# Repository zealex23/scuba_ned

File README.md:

# SCUBA Near Eye Display

A Near Eye Display dive computer for SCUBA Divers.

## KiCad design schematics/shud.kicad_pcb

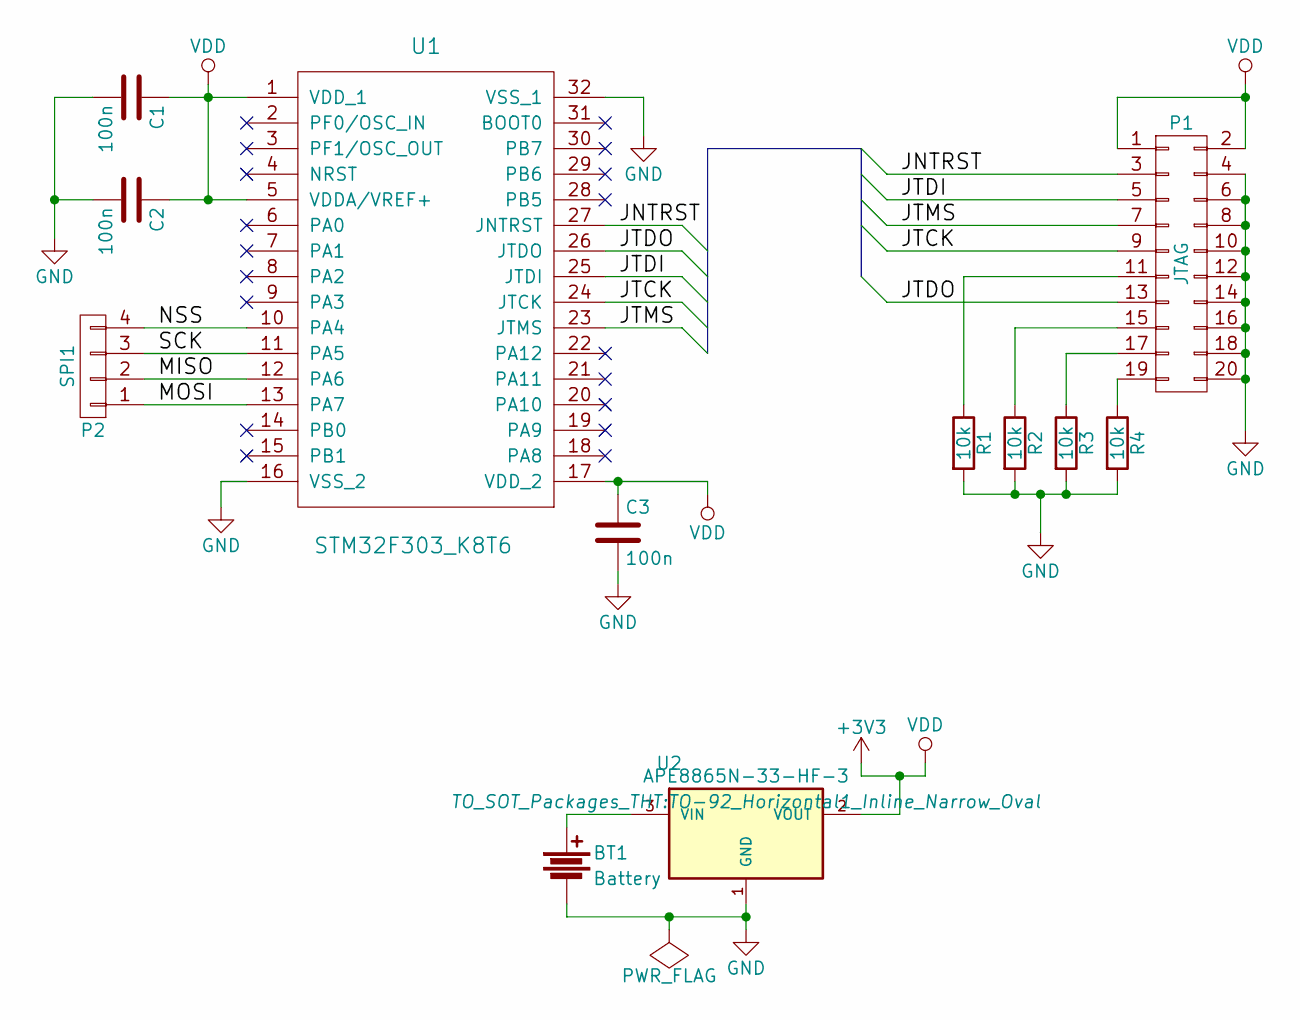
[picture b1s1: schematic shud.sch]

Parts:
BT1: Battery; TerminalBlock_Pheonix_MKDS1.5-2pol
C1, C2, C3: 100n; C_Disc_D3_P2.5
P1: JTAG; Pin_Header_Straight_2x10
P2: SPI1; Pin_Header_Straight_1x04
R1, R2, R3, R4: 10k; Resistor_Horizontal_RM10mm
U1: STM32F303_K8T6; LQFP-32_7x7mm_Pitch0.8mm
U2: APE8865N-33-HF-3; TO-92_Horizontal1_Inline_Narrow_Oval

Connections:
+3V3: C1.1, C2.1, C3.1, P1.1, P1.2, U1.1 (VDD_1), U1.5 (VDDA/VREF+), U1.17 (VDD_2), U2.2 (VOUT)
/JNTRST: P1.3, U1.27 (JNTRST)
/JTCK: P1.9, U1.24 (JTCK)
/JTDI: P1.5, U1.25 (JTDI)
/JTDO: P1.13, U1.26 (JTDO)
/JTMS: P1.7, U1.23 (JTMS)
/MISO: P2.2, U1.12 (PA6)
/MOSI: P2.1, U1.13 (PA7)
/NSS: P2.4, U1.10 (PA4)
/SCK: P2.3, U1.11 (PA5)
GND: BT1.2, C1.2, C2.2, C3.2, P1.4, P1.6, P1.8, P1.10, P1.12, P1.14, P1.16, P1.18, P1.20, R1.2, R2.2, R3.2, R4.2, U1.16 (VSS_2), U1.32 (VSS_1), U2.1 (GND)
unnamed: BT1.1, U2.3 (VIN)
unnamed: P1.11, R1.1
unnamed: P1.15, R2.1
unnamed: P1.17, R3.1
unnamed: P1.19, R4.1

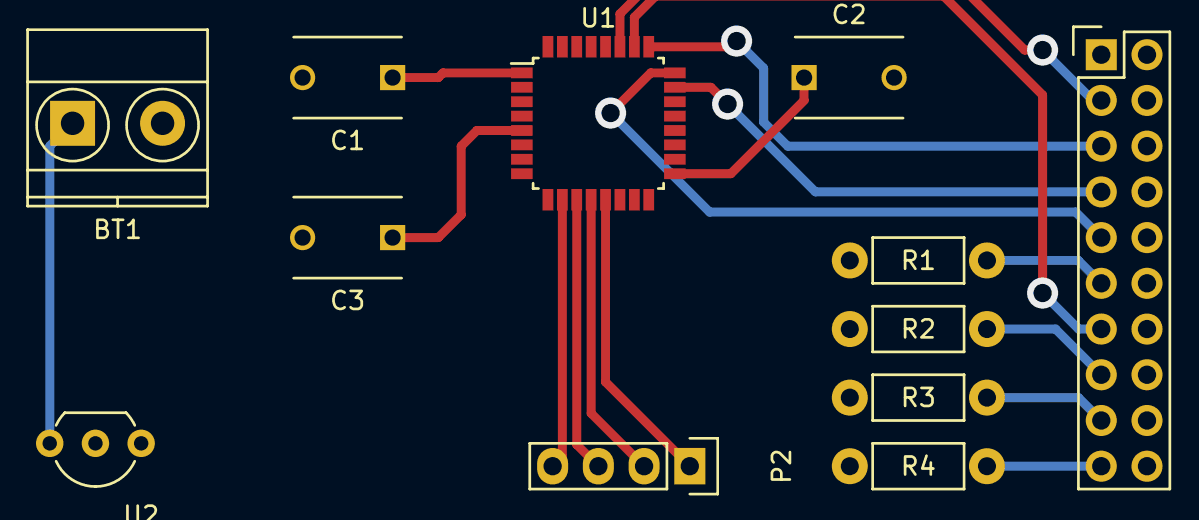
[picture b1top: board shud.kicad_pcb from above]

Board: 2 copper layers, 12 parts (0 on the bottom side), 16 nets.

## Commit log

2016-06-22 initial commit of firmware
2016-06-22 add README
2016-06-22 add schematic link to oled
2016-06-22 add stuff to BOM
2016-06-22 add more bom stuff
2016-06-22 change circular oled to rectangular
2016-06-23 add pressure sensor
2016-06-23 move bom
2016-06-23 change tabs to commas
2016-06-23 escape quote
2016-06-23 remove quote
2016-06-23 remove comma
2016-06-23 add sparkfun breakout
2016-06-23 add missing commas
2016-06-23 add missing comma
2016-06-23 add pressure sensor price
2016-06-23 Use K8T6 instead of VCT6
2016-06-25 add openocd config
2016-06-29 pitch
2016-06-30 create schematic
2016-06-30 finish pcb
2016-06-30 change pad clearance
2016-06-30 change footprints
2016-06-30 mirror
2016-07-01 write script
2016-07-01 start writing conclusion
2016-07-01 change to second level headers
